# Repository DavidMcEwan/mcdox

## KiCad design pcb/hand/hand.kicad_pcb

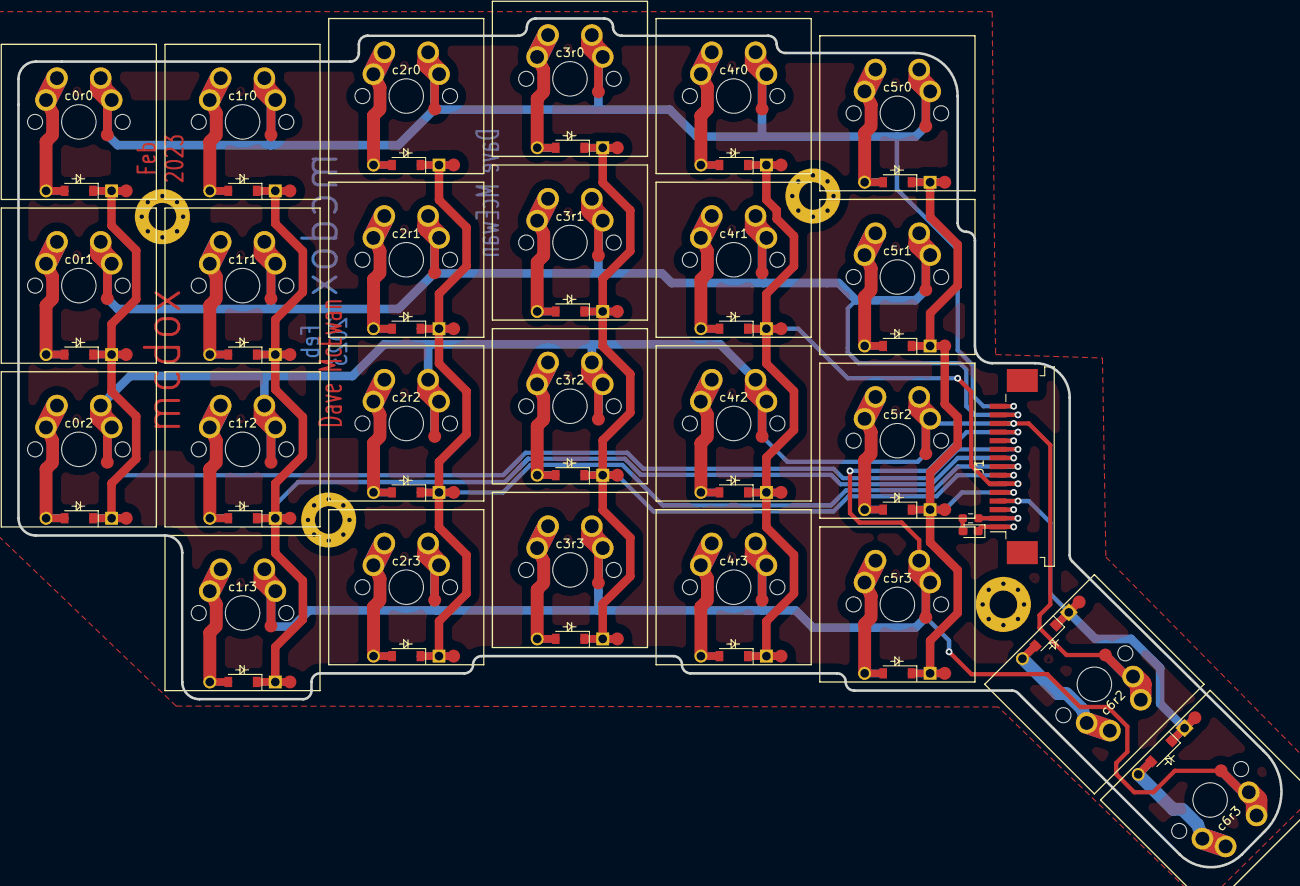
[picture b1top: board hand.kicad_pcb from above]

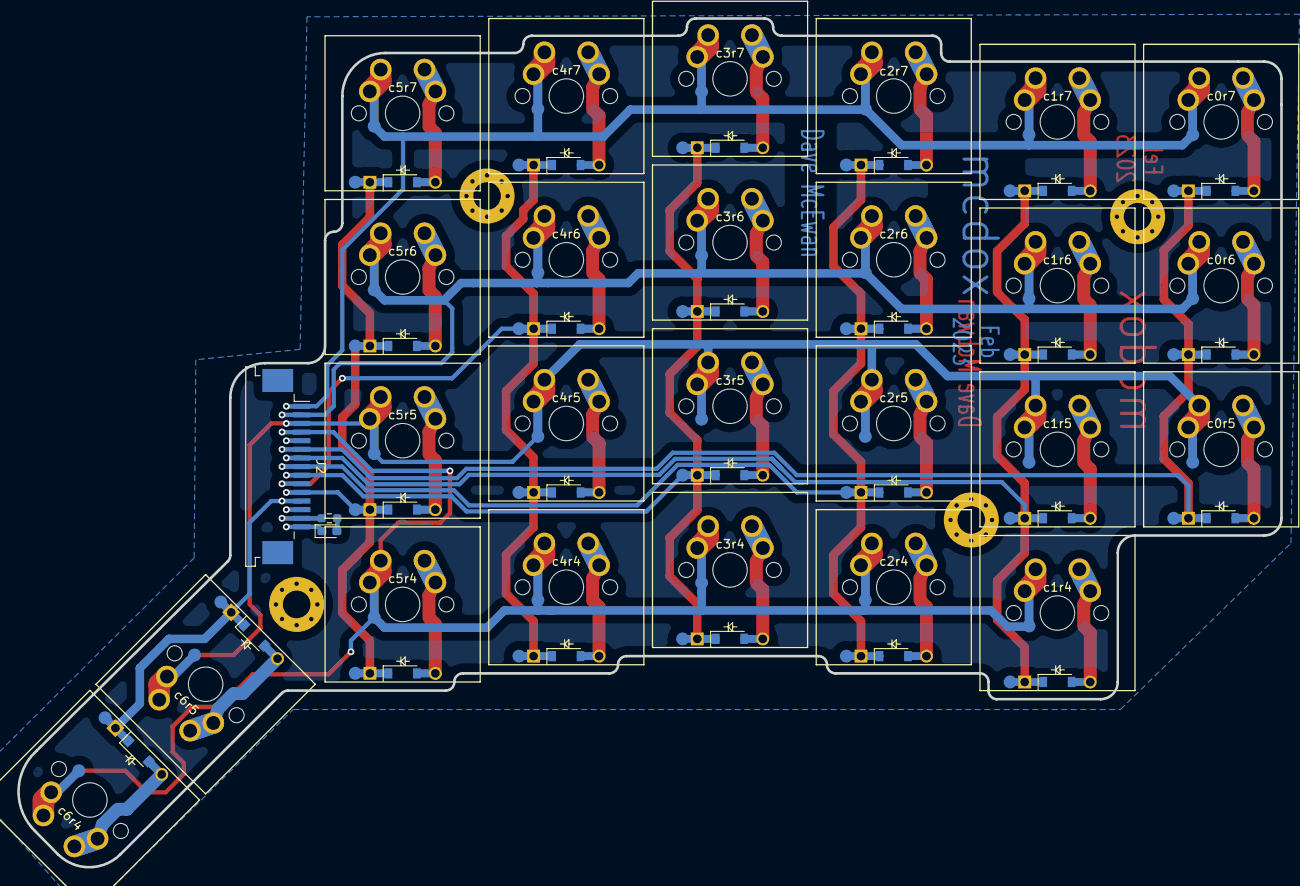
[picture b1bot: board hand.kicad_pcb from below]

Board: 2 copper layers, 146.6 x 98.5 mm, 35 parts (5 on the bottom side), 17 nets.

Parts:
H1, H2, H3, H4: MountingHole_3.2mm_M3_Pad_Via
J1, J2: Conn_01x15; TE_1-84953-5_1x15-1MP_P1.0mm_Horizontal
LED1, LED2: LED; D_0603_1608Metric_Pad1.05x0.95mm_HandSolder
R1, R2: 220; R_0603_1608Metric_Pad0.98x0.95mm_HandSolder
c0r0, c0r1, c0r2, c1r0, c1r1, c1r2, c1r3, c2r0, c2r1, c2r2, c2r3, c3r0, c3r1, c3r2, c3r3, c4r0, c4r1, c4r2, c4r3, c5r0, c5r1, c5r2, c5r3, c6r2, c6r3: switchDiode; reversibleMX_10u

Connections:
+3V3: J1.2, J2.14, R1.1, R2.1
GND: J1.1, J2.15, LED1.1, LED2.1
unnamed: LED1.2, R1.2
unnamed: LED2.2, R2.2
col0: J1.10, J2.6, c0r0.2, c0r1.2, c0r2.2
col1: J1.9, J2.7, c1r0.2, c1r1.2, c1r2.2, c1r3.2
col2: J1.8, J2.8, c2r0.2, c2r1.2, c2r2.2, c2r3.2
col3: J1.7, J2.9, c3r0.2, c3r1.2, c3r2.2, c3r3.2
col4: J1.6, J2.10, c4r0.2, c4r1.2, c4r2.2, c4r3.2
col5: J1.5, J2.11, c5r0.2, c5r1.2, c5r2.2, c5r3.2
col6: J1.4, J2.12, c6r2.2, c6r3.2
col7_NC: J1.3, J2.13
row0: J1.15, J2.1, c0r0.1, c1r0.1, c2r0.1, c3r0.1, c4r0.1, c5r0.1
row1: J1.14, J2.2, c0r1.1, c1r1.1, c2r1.1, c3r1.1, c4r1.1, c5r1.1
row2: J1.13, J2.3, c0r2.1, c1r2.1, c2r2.1, c3r2.1, c4r2.1, c5r2.1, c6r2.1
row3: J1.12, J2.4, c1r3.1, c2r3.1, c3r3.1, c4r3.1, c5r3.1, c6r3.1
row4_NC: J1.11, J2.5

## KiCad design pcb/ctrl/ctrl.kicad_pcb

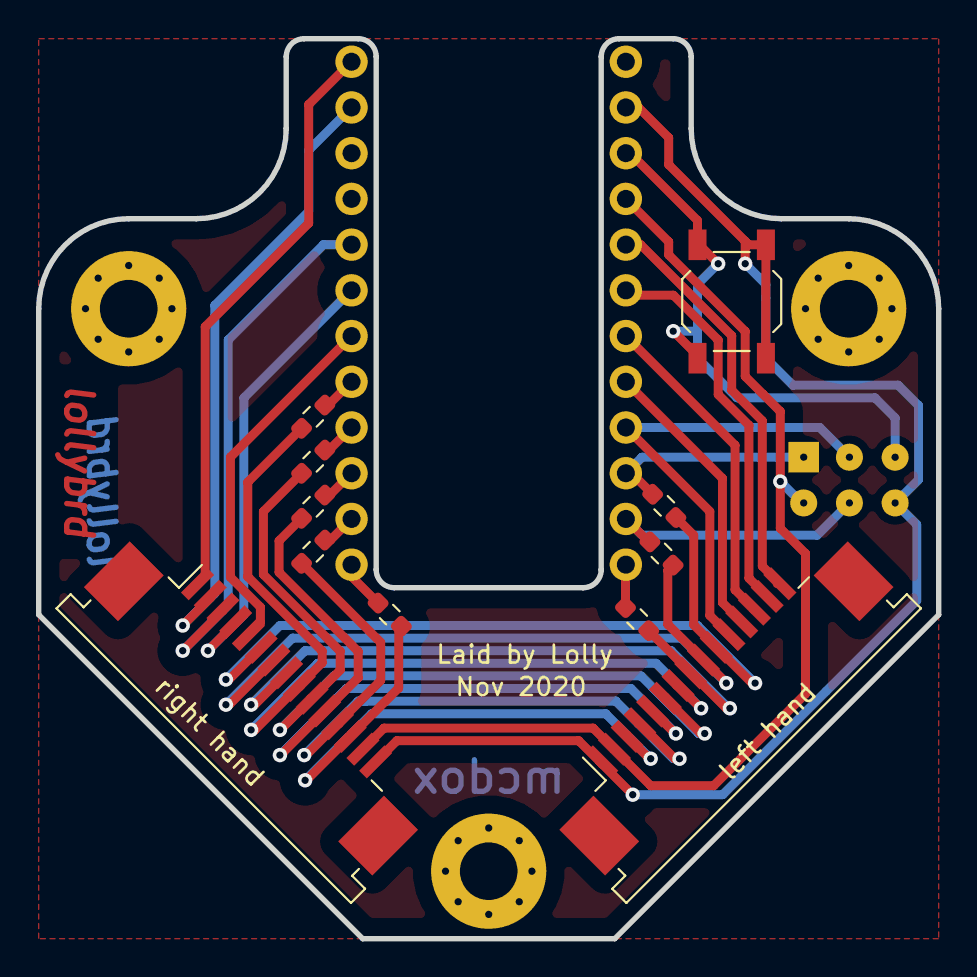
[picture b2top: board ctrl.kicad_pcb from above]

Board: 2 copper layers, 50.0 x 50.0 mm, 13 parts (1 on the bottom side), 29 nets.

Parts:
ICSP: Conn_02x03_Odd_Even; PinHeader_2x03_P2.54mm_Vertical
Jleft1: Conn_01x15; TE_1-84953-5_1x15-1MP_P1.0mm_Horizontal
Jright1: Conn_01x15; TE_1-84953-5_1x15-1MP_P1.0mm_Horizontal
R0, R1, R2, R3, R4, R5, R6, R7: 220; R_0603_1608Metric_Pad0.98x0.95mm_HandSolder
SW1: SW_Push; SW_SPST_TL3342
U1: ArduinoProMicro

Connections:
GND: ICSP.6, Jleft1.1, Jright1.15, SW1.2, U1.14
MISO: ICSP.1, R0.2, U1.22
MOSI: ICSP.4, R1.2, U1.23
unnamed: R2.2, U1.24
unnamed: R3.2, U1.12
unnamed: R4.2, U1.11
unnamed: R5.2, U1.10
unnamed: R6.2, U1.9
unnamed: R7.2, U1.8
RST: ICSP.5, SW1.1, U1.15
SCK: ICSP.3, Jleft1.11, U1.21
VCC: ICSP.2, Jleft1.2, Jright1.14, U1.16
col0: Jleft1.10, Jright1.6, R0.1
col1: Jleft1.9, Jright1.7, R1.1
col2: Jleft1.8, Jright1.8, R2.1
col3: Jleft1.7, Jright1.9, R7.1
col4: Jleft1.6, Jright1.10, R6.1
col5: Jleft1.5, Jright1.11, R5.1
col6: Jleft1.4, Jright1.12, R4.1
col7: Jleft1.3, Jright1.13, R3.1
row0: Jright1.1, U1.1
row1: Jright1.2, U1.2
row2: Jright1.3, U1.5
row3: Jright1.4, U1.6
row4: Jright1.5, U1.7
row6: Jleft1.12, U1.20
row7: Jleft1.13, U1.19
row8: Jleft1.14, U1.18
row9: Jleft1.15, U1.17

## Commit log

2022-01-14 case.svg Move weight-saving cut to avoid filling with dust.
2022-01-14 case.svg Increase margin on coverTop to avoid squeeky keycaps.
2022-01-14 case.svg Move PCB cutouts to ease plugging FPC cables.
2023-01-21 case Remove 2 bolts.
    - Enlarge weight-saving cutout.
    - Add cutouts to innerTop.
    - Remove/move bolts under wrists.
    - New bolt position should fit more nicely into base of thumb/palm.
2023-01-21 case Note violation on innerTop.
2023-01-21 case Name layers in layerstack.svg to match case.svg
2023-01-21 experimental/keymap_mcdox3 Alt more easily available.
2023-01-21 case/layerstack Add dev copy for things I'm unsure about.
2023-01-21 pcb/hand Reduce switch array to 5 rows, 6 columns.
    - Simple intuitive mapping in sw.
    - Requires 16 GPIO for a pair. (6 + 2*5)
2023-01-21 pcb/hand Rearrange switch array to 4 rows, 7 columns.
    - Less intuitive mapping in sw, but can use a pp macro.
    - Requires 15 GPIO for a pair. (7 + 2*4)
2023-01-21 pcb/hand 1u keycaps for all switches
2023-01-21 pcb/hand NC to clean up most DRC
2023-01-21 pcb/hand Begin layout and edges.
2023-01-27 pcb/hand Layout finger cluster.
2023-01-27 pcb/hand Route and fill
2023-01-27 pcb/hand Begin tidying DRC.
    TODO:
    - Name
    - Date
    - Connect J1 to J2
    - Finish DRC
2023-02-05 pcb/hand Recess cutout under switches on Eco2.User
    Remove all the pad-to-pad tracks too... Loads of them!
2023-02-05 pcb/hand Full layout.
2023-02-05 pcb/hand Generate SVG for case.
2023-02-19 case Remove layerstack_dev and layerstack_future
2023-02-19 case Complete revamp of layerstackPalette.
2023-02-24 layerstack Draw plan for 5x3mm
2023-03-12 case PCB and outline placement.
    Can fit all 5 layers on a single 400x600mm sheet.
2023-03-17 case First draft of mount and coverBottom. Started pcbProfile.
2023-03-24 case Reduce socket hole diameters to from 6mm to 5.4mm
    Looks like too much space on my current red/black one.
2023-03-24 case Group parts on pcb.F.Fab
    Preparation for (maybe) moving ctrl upwards.
2023-03-24 case cut.innerTop
